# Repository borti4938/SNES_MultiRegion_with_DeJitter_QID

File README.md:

## Multi-Region Mod for any SNES

**Free your SNES**

(picture shows last prototype PCB installed on a SNS-CPU-RGB-01)

### Acknowledgement and Licensing

This PCB, its idea and design, is a confluence of multiple projects. All credits and rights are going to their respective creators:

- **SuperCIC-lock** by Ikari_01
  Copyright (c) 2010 by Maximilian Rehkopf under GNU GPLv2
  Source: [sd2snes homepage](https://sd2snes.de/blog/cool-stuff/supercic)
- **uIGR** by Ikari_01 and borti4938
  Copyright (c) 2010 by Maximilian Rehkopf under GNU GPLv2,
  and modifications copyright (c) 2015 by Peter Bartmann under GNU GPLv2
  Source: [sd2snes homepage](https://sd2snes.de/blog/cool-stuff/in-game-reset), [this repository](./fw/uIGR)
- **Region Patch** built in SNES by Ikari_01 (initial idea and detection using SuperCIC-lock) and borti4938 (schematic refinement and CPLD implementation)
  Initial idea (c) 2012 ikari_01, CPLD implementation as used here covered in DeJitter license
  Source: [sd2snes homepage](https://sd2snes.de/files/supercic-213f.pdf)
- **DeJitter** by marqs85
  Copyright (c) 2017-2018 Markus Hiienkari under MIT
  and modifications and additions copyright (c) 2019 Peter Bartmann under MIT
  Source: [Original GitHub Repository](https://github.com/marqs85/snes_dejitter), [this repository](./fw/Logic)
- **DFO** by micro
  Copyright / created 2015 by Jakob Schäfer without licensing (but given to retro community)
  Source: mirror in [this repository](./fw/dfo), with minor adaptations and with several original sources noted [in the Source.md file](./fw/dfo/SOURCE.md)
- **PCB design** by borti4938
  Copyright (c) 2019 by Peter Bartmann under GNU GPLv3

### Features and Functions

##### In short

- **SuperCIC:** lockout chip replacement 50Hz/60Hz switch cabability
- **uIGR:** controller input sniffing to perform certain actions like reset or 60Hz and 50Hz switch up on certain combinations
- **Region Patch:** overrides region protection based on picture processing status reads
- **DeJitter:** removes jitter on sync for NTSC mode
- **DFO:** dual frequency oscillator, here used to switch between base clocks for 50Hz, 60Hz video-modes

##### SuperCIC

Hold down the reset button in order to swipe through 50Hz (green LED), 60Hz (red LED) or Auto-Region (yellow LED).

With the sd2snes you are able to pair the SuperCIC with the flash card. Then you'll be able to switch between 60Hz and 50Hz mode. However, you need to have the uIGR, which is master for the region setting, in SuperCIC pass through mode. Some more information is given [below](https://github.com/borti4938/SNES_MultiRegion_with_DeJitter_QID#using-a-modded-snes-with-flashcards).

##### uIGR

The uIGR sniffs the controller inputs directly at the controller port. Therefor it is able to detect certain button combinations. All button combinations are collected in an overview PDF, which is available in [German](https://github.com/borti4938/SNES_MultiRegion_with_DeJitter_QID/blob/master/fw/uIGR/Manuals/uIGR_Anleitung.pdf) and [English](https://github.com/borti4938/SNES_MultiRegion_with_DeJitter_QID/blob/master/fw/uIGR/Manuals/uIGR_Manual.pdf). Here are the most important ones:

- Region forcing:
  - 60Hz: L + R + Select + A
  - 50Hz: L + R + Select + Y
  - Auto: L + R + Select + B
  - S-CIC pass through: L + R + Select + D-pad left OR L + R + Select + D-pad right
- Reset:
  - simple reset: L + R + Select + Start
  - double reset (back to main menu of sd2snes): L + R + Select + X

##### Region Patch

Overwrites region if game request register $213F, where bit 4 represents the region. Region patching can be disabled (see [uIGR PDFs](https://github.com/borti4938/SNES_MultiRegion_with_DeJitter_QID/tree/master/fw/uIGR/Manuals)). You also have to consider switching off the region patch if using non-original cartridges or [flash cards](https://github.com/borti4938/SNES_MultiRegion_with_DeJitter_QID#using-a-modded-snes-with-flashcards) (sd2snes with Pairmode with SuperCIC is not a problem).

##### DeJitter

In NTSC mode the SNES outputs a shorter scanline in non-visible area. This might be an issue for certain TVs if you use pure analog to digital conversion without frame buffer like the OSSC does. DeJitter 'removes' this shorter line by pausing the clock for a few cycles.

As drawback this mechanic varies output timing a bit, however the inaccuracy is neglectable when comparing it to clock variations throughout different consoles.

At the moment, DeJitter is enabled by default and can only be disabled by setting jumper _SJ31_.

##### DFO

Short for dual frequency oscillator. Actually in combination with the CPLD this allows to switch between three output clocks plus two color carrier clocks. If modding board is correctly installed, there is nothing special to consider here.

### PCB Description

#### Solder Pads

These are just general descriptions of the in- and outputs. Please refer to the installation instructions for each [specific mainboard version](./installation/) (if exists) for suitable connections.

- **/Rst.o:** (output (2x))
  Low-active reset output. This has to be connected with CIC-lock pad 10 / S-APU pin 100. Connect either pad.
- **Rst.i:** (input)
  High-active reset input. This pad has to be connected with the CIC-lock pad 8 (reset button).
- **LED.Re:** (output)
  LED driver for replacement LED; usually red. Output is active on 60Hz and auto video mode and off on 50Hz (or vice versa if SJ21 is set (common anode LED))
- **LED.Gr:** (output)
  LED driver for replacement LED; usually green. Output is active on 50Hz and auto video mode and off on 60Hz (or vice versa if SJ21 is set (common anode LED))
- **Ctrl.port.10:** (input)
  Input for controller 1 sniffing (data latch signal). _Port_ refers to flat cable connector of the whole controller panel, i.e. pin is equivalent for controller connector pin 3.
- **Ctrl.port.8:** (input)
  Input for controller 1 sniffing (data clock signal). _Port_ refers to flat cable connector of the whole controller panel, i.e. pin is equivalent for controller connector pin 2.
- **Ctrl.port.6:** (input)
  Input for controller 1 sniffing (serial data signal). _Port_ refers to flat cable connector of the whole controller panel, i.e. pin is equivalent for controller connector pin 4.
- **Vmode:** (output)
  Output sets the PPU video mode at S-PPU1 pin 24 and S-PPU2 pin 30 or at the S-CPUN pin 111. Output is active on 50Hz mode and inactive on 60Hz mode.
- **/Vmode:** (output (2x))
  Output sets the video encoding at the video encoder, which is pin 19 of the S-ENC and pin 9 of the S-RGB. Connect just on of the pads!
- **Clk.CIC:** (input)
  Input for the SuperCIC-lock clock, which comes from CIC pad 7.
- **MClk.o:** (output)
  Output for the (de-jittered) master clock of the SNES. This is approx. 21.477MHz in NTSC mode and appr. 17.734MHz (1Chip-SNES, SJ32 not set) or appr. 21.281MHz (non-1Chip, SJ32 set) in PAL mode. Please refer to the general installation note to see whether and how to connect this pad properly.
- **CClk.o:** (output)
  Output of the color carrier, which is appr. 3.380MHz in NTSC mode and appr. 4.433MHz in PAL mode. Please refer to the general installation note to see whether and how to connect this pad properly.
- **/CS.i:** (input (2x since SMR20190813)
  Input of the 'original' (non-de-jittered) composite sync. This comes from pin 100 S-PPU2 or pin 151 S-CPUN.
- **/CS.o buf:** (output)
  Buffered (de-jittered) composite sync output. This is meant to be connected directly to the multiout pin 3. Note: The PAL SNES has 12V connected to this pin, which has to be removed.
- **/CS.o raw:** (output (2x))
  Raw output of the CPLD, which has 3.3V high and 0V low level. Connect it to the video encode, which is pin 8 of the S-ENC or pin 7 of the S-RGB (both chips allows 2.0V for input high, so 3.3V high is sufficient.)

#### Jumper

- **SJ11:** alternative clock for the SuperCIC; close this jumper if you don't connect the _Clk.CIC_ pad in order to use the clock meant for the CIC-key
- **SJ21:** close this jumper if you use a LED with a common anode. Otherwise leave this jumper untouched
- **SJ31:** closing this jumper permanently disables the de-jitter function. This solder jumper is a bit larger to give the installer the option to connect a slide switch here (_speed-runner discussions_).  
   - There is also an issue opened in [marqs85 DeJitter repository](https://github.com/marqs85/snes_dejitter/issues/9) reported by [BambooShadow](https://github.com/BambooShadow), which states that composite video and s-video becomes flickery. This is probably related to the S-RGB encoder chip on SNS-CPU-RGB-01 and later models (PAL: SNSP-CPU-1CHIP-01 and later). In any case, you can disable DeJitter if this is also an issue for you.  
   - I personally recommend to turn DeJitter off. Turn DeJitter only on if you use simple line doublers like the OSSC and if you have any issue on getting a proper picture.
- **SJ32:** short this jumper if the board is installed in a non-1Chip-SNES (SNES Jr. / SNES2 are also 1Chip-SNES)
- **SJ61:** distributes clock output to cartridge slot pin 1. This jumper **must not** be closed in 1Chip-SNES. Side note: if SJ32 is open, SJ61 has to open, too.
- **SJ63:** (since SMR20200323) decides which color carrier is forwarded to output. This jumper has two option; you must not close both jumpers!
  - SJ63.1: (marked with a dot) outputs color carrier derived from non-dejittered clock.  
    Use this if you have a problem with discoloring on composite video or S-Video ([issue thread at shmups](https://shmups.system11.org/viewtopic.php?p=1389666#p1389666))  
    Btw: this is default for all earlier version of the modding board flashed with the current firmware. If you need the other color carrier, just go back to a previous version.
  - SJ63.2: outputs color carrier derived from dejittered clock.  
    (I personally need to use this clock as my TV does not like the color carrier from non-dejittered clock)
  - Again: **You must not close both jumpers!**
- **SJ93**: (since SMR20200323) controls sync level of buffered csync output. Sync level:
  - opened: appr. 1.87V @ 75ohm termination i.e. needs a resistor inside the sync wire further attanuating the signal. Designed to work for cables with 470 ohm resistor inside resulting in appr. 450mV @ 75ohm termination
  - closed: appr. 300mV @ 75ohm termination suitable for pass through wired cables at sync, works with standard TV / scaler setup

#### Firmware

U1, U2, U3 and U5 need a firmware flashed to the chip. U1 and U2 have to be programmed prior to assembly whereas the PCB provides ICSP headers for the other ones.

- **U1:** PIC 16F630 microcontroller with - [SuperCIC-lock firmware](http://sd2snes.de/files/supercic.zip)
- **U2:** PIC 16F684 microcontroller with [uIGR firmware](https://raw.githubusercontent.com/borti4938/SNES_MultiRegion_with_DeJitter_QID/master/fw/uIGR/snes_uigr_684_with_lock.hex)

Use a PICKit, TL866CS or similar programmer.

- **U3:** _ATMEL_ CPLDs: ATF1502ASV or ATF1504ASV(L) CPLD with clock switch, region patch and de-jitter firmware. Pre-build firmware only supports SMR20190813 (and later) modding boards.

  - [ATF1502ASV](https://github.com/borti4938/SNES_MultiRegion_with_DeJitter_QID/raw/master/fw/Logic/output_files/multi_func_atmel/multi_function.svf)
  - [ATF1504ASV(L)](https://github.com/borti4938/SNES_MultiRegion_with_DeJitter_QID/raw/master/fw/Logic/output_files/multi_func_atmel/multi_function_64.svf)
  
Use an OpenOCD compatible JTAG programmer. I tested the workflow with an [Adafruit FT232H Breakout Board](https://www.adafruit.com/product/2264), yet you can use any other JTAG programmer that supports 3.3V IO signal levels.

1. Create an openocd.conf that matches your JTAG programmer. A configuration files for FT2232-based and FT2232H programmers are found in the [firmware folder](./fw/Logic/output_files/multi_func_atmel/). They use following standard pinout for data signals:  
  - ADBUS0 -> TCK
  - ADBUS1 -> TDI
  - ADBUS2 -> TDO
  - ADBUS3 -> TMS
2. Connect the JTAG programmer the modding board, except for Vref! Power the board via 5V during programming.  This can be done by using the DFO programmer connected with V_target set to 5V (or 3.3V) if the modding board is not installed yet (other power solutions are possible, but please use the 5V power supply rail to not harm the DC converters. Or you can simply switch on the SNES for programming. Of course, the CPLD can be also flashed prior to assembly if you have a proper adapter at hand.
3. Initialize the JTAG connection:  
~~~~
openocd -f openocd-ft2232h.conf
~~~~  
OpenOCD should detect the JTAG chain without any errors. If you have any, just double-check if everything is well connected and the CPLD is powered.

4. When successful, open another terminal to interact with openocd and program the chip:  
~~~~
telnet localhost 4444
> svf <full_path_to_svf_file>
~~~~  
Wait for the program to be finished.

- **U3:** _obsolete Altera / intelFPGA CPLDs_: EPM7032 or EPM7064 CPLD with clock switch, region patch and de-jitter firmware. You have to choose the right one depending on your modding board version.

  - [Version SMR20190813 (and later), EPM7032](https://github.com/borti4938/SNES_MultiRegion_with_DeJitter_QID/raw/master/fw/Logic/output_files/multi_func/multi_function.pof)
  - [Version SMR20190813 (and later), EPM7032](https://github.com/borti4938/SNES_MultiRegion_with_DeJitter_QID/raw/master/fw/Logic/output_files/multi_func/multi_function_64.pof)
  - [Version SMR20190603 and earlier](https://github.com/borti4938/SNES_MultiRegion_with_DeJitter_QID/raw/master/fw/Logic/output_files/multi_func_legacy/multi_func_legacy.pof)

Use an Altera USB Blaster (or clone) for flashing the firmware.

After assembly, the modding board has to be powered for flashing the firmware. This can be done by using the DFO programmer connected with V_target set to 5V (or 3.3V) if the modding board is not installed yet (other power solutions are possible, but please use the 5V power supply rail to not harm the DC converters. Or you can simply switch on the SNES for programming. Of course, the CPLD can be also flashed prior to assembly if you have a proper adapter at hand.

- **U5:** CDCE913 with [appropriate configuration](https://raw.githubusercontent.com/borti4938/SNES_MultiRegion_with_DeJitter_QID/master/fw/dfo/clockpro/snes_multi_region.hex)

Use the DFO programmer to flash the PLL. The [DFO readme](./fw/dfo/SOURCE.md) describes how to properly perform the flashing.
I alternatively wrote a [program for Arduino boards](./fw/dfo/arduino/) to flash the CDCE913 with the I2C interface of the Arduino.
I tested the code with an Arduino Nano and Arduino Nano Every.

### Installation Notes

#### Manufacturing the PCB

You can choose any manufacturer which you prefer. All files for manufacturing including the design files are provided in subfolder [pcb/gerber/pcb/](./pcb/gerber/pcb/). As the PCB is designed in EAGLE (current version 7.4.2), gerbers are exported in the actual format. However, some services have problem while automatically analyze those like OSHPark or JCLPCB. Please try the older format in [pcb/gerber/pcb.eagle_legacy_export/](./pcb/gerber/pcb.eagle_legacy_export/).

**IMPORTANT**
Please use a substrate thickness of 0.8mm in order to make installation easier.

#### Assembly

##### Sourcing the Parts

For sourcing the parts, please be referred to the [Bill Of Materials](https://github.com/borti4938/SNES_MultiRegion_with_DeJitter_QID/blob/master/pcb/BOM.xlsx?raw=true)

##### Soldering

The PCB is designed with having hand soldering in mind. Most complicated footprints are probably the 44TQFP package of the CPLD or the 14TSSOP of the CDCE913.

However, if you plan to use a stencil, you can use the [stencil gerber file](./pcb/gerber/stencil/SNES_MR_DeJitter_QID.GTP). All SMDs are placed in top layer.

**IMPORTANT**
SuperCIC (PIC16F630-I/SL) and uIGR (PIC16F684-I/SL) need firmware flashed prior to soldering as mentioned later in this document.

#### Installation

This is not a complete installation manual. It's moreover a general overview on _'HowTo'_. Installation manuals are provided in the [subfolder installation](./installation/) once ready. I cannot test every single mainboard revision (there are too many out there), so the installation folder will grow from time to time once I see a proper report of an installation or I did an installation on a specific mainboard version on my own.

##### Preparation of SNES

###### General Steps

- remove original CIC-lock (or at least lift pins 1, 2, 10 and 11)
- remove LED from front panel (large SNES only)

###### Specific Steps for 1Chip-SNES

- lift pin 111 from S-CPUN
- remove X1
- lift pin 9 from S-RGB (or cut encoding mode jumper at bottom side of SNES mainboard (NTSC board revisions))

###### Specific Steps for Non-1Chip-SNES

- lift pin 24 of S-PPU1 and pin 30 of S-PPU2
- disconnect Master-Clock
  - SNSP-CPU-01/02: lift pin 4 of the S-CLK or remove R73 (0ohm jumper)
  - different methods for NTSC mainboards
- lift CSYNC input pin of the video encoder
  - pin 8 of S-ENC
  - pin 7 of S-RGB
- if you want to switch color carrier:
  - PAL: lift pin 5 of the S-CLK
  - NTSC: lift pin 3 of the S-PPU2
  - SNES with S-ENC: lift pin 19 (or cut encoding mode jumper at bottom side of SNES mainboard (NTSC board revisions))
  - SNES with S-RGB: lift pin 9 (or cut encoding mode jumper at bottom side of SNES mainboard (NTSC board revisions)) 

##### Installation of PCB

###### General Steps

- Solder PCB in place under the cartridge slot. Be aware of the orientation (pin marking must match)
- put the replacement dual LED where the original was (use a small piece of hot glue if needed)...  
... or in SNES2 / Jr. think of a good place where the replacement LED can be if you want to use it...  
... and connect the common pole to either _Ground_ or _Vcc_ (common cathod or anode, respectively)
- connect pads _Rst.o, Rst.i, LED.Re, LED.Gr, Ctrl.port.10-6, Vmode, /CS.i, /CS.o (raw)_ according to their description
- either connect _Clk.CIC_ pad (preferable) or close jumper _SJ11_
- close jumper _SJ21_ if you use a LED with common anode

###### Specific Step for 1Chip-SNES

- connect _MCLK.o_ to X1 (the side which is connected to S-CPUN pin 9)
- connect _/Vmode_ to S-RGB pin 9
- (color carrier is switched by S-CPUN so there is no need to connect _CClk.o_)

###### Specific Step for Non-1Chip-SNES 

- close _SJ32_ and _SJ61_
- if you plan to switch color carrier:
  - connect _CClk.o_ to either pad 3 of S-PPU2 (NTSC) or to pad 5 of S-CLK (PAL)
  - connect _/Vmode_ to S-ENC pin 19 / S-RGB pin 9 

### Using a Modded SNES with Flashcards

In general, using flashcards like the sd2snes, SuperEverdrive and PowerPak together with the **region patching** activated is not a good idea. I try to explain why!

First of all, one has to understand how a region patch works. In the S-PPU2 register $213F bit 4 shows whether the SNES is running in NTSC-mode or in PAL-mode (set up using S-PPU2 pin 30 or S-CPUN pin 111). Many games are checking this register on start-up (or during the gameplay) and check the value on bit 4. NTSC-games expect a '0' whereas PAL-games a '1'. If the bit does not return the required value, the game ends with _'This gamepak is not designed for your SFC/SNES'_ or similar.
A region patch observes the address bus B and recognizes a request of $213F. Then the patch forces on the data bus bit 4 GND or Vcc by simply 'beating'/'overdriving' the output of the S-PPU2.

An important point is how the region patch 'knows' which value has to be written.
On this modding PCB the SuperCIC-lock outputs the value on pin 3. The bit is determined using the CIC-key found on the cartridge. And this is the point where flash-cards become 'critical' for the region patch. As the SuperCIC-lock only checks the region of the cartridge using the CIC-key, the SuperCIC-lock CANNOT know which region the loaded ROM is. The overwritten value on bit 4 during a $213F request might be incorrect!
As flashcards have there own region patching (at least the sd2snes; I don't own a SuperEverdrive or PowerPak) you can simply switch off the region patch of the modding PCB (using Sel+L+R+Dw; LED-code: red-off-red).

#### A very last remark to the sd2snes:
As the SuperCIC-lock is part of the sd2snes project, there is another solution: the so-called 'Pairmode'.
The pairmode is available with the firmware v0.1.7 preview 4 or later. In the Pairmode the SuperCIC-lock goes into a pairmode-loop with the sd2snes. In this loop, forced region, LED status and the ROM region is constantly updated.

To change the forced region (and thus the LED-state) using the sd2snes (via the config.yml or the option GUI -> SuperCIC Settings), the uIGR has to be in the SuperCIC-mode (using Sel+L+R+Le / Sel+L+R+Ri) as the uIGR is master and the SuperCIC-lock slave regarding the region set to the SNES.
As the ROM region is updated constantly, the region patch on the modding PCB can be left on. I recommend to switch the sd2snes-own region patch off in this case (via the config.yml or the option GUI -> In-game Settings).

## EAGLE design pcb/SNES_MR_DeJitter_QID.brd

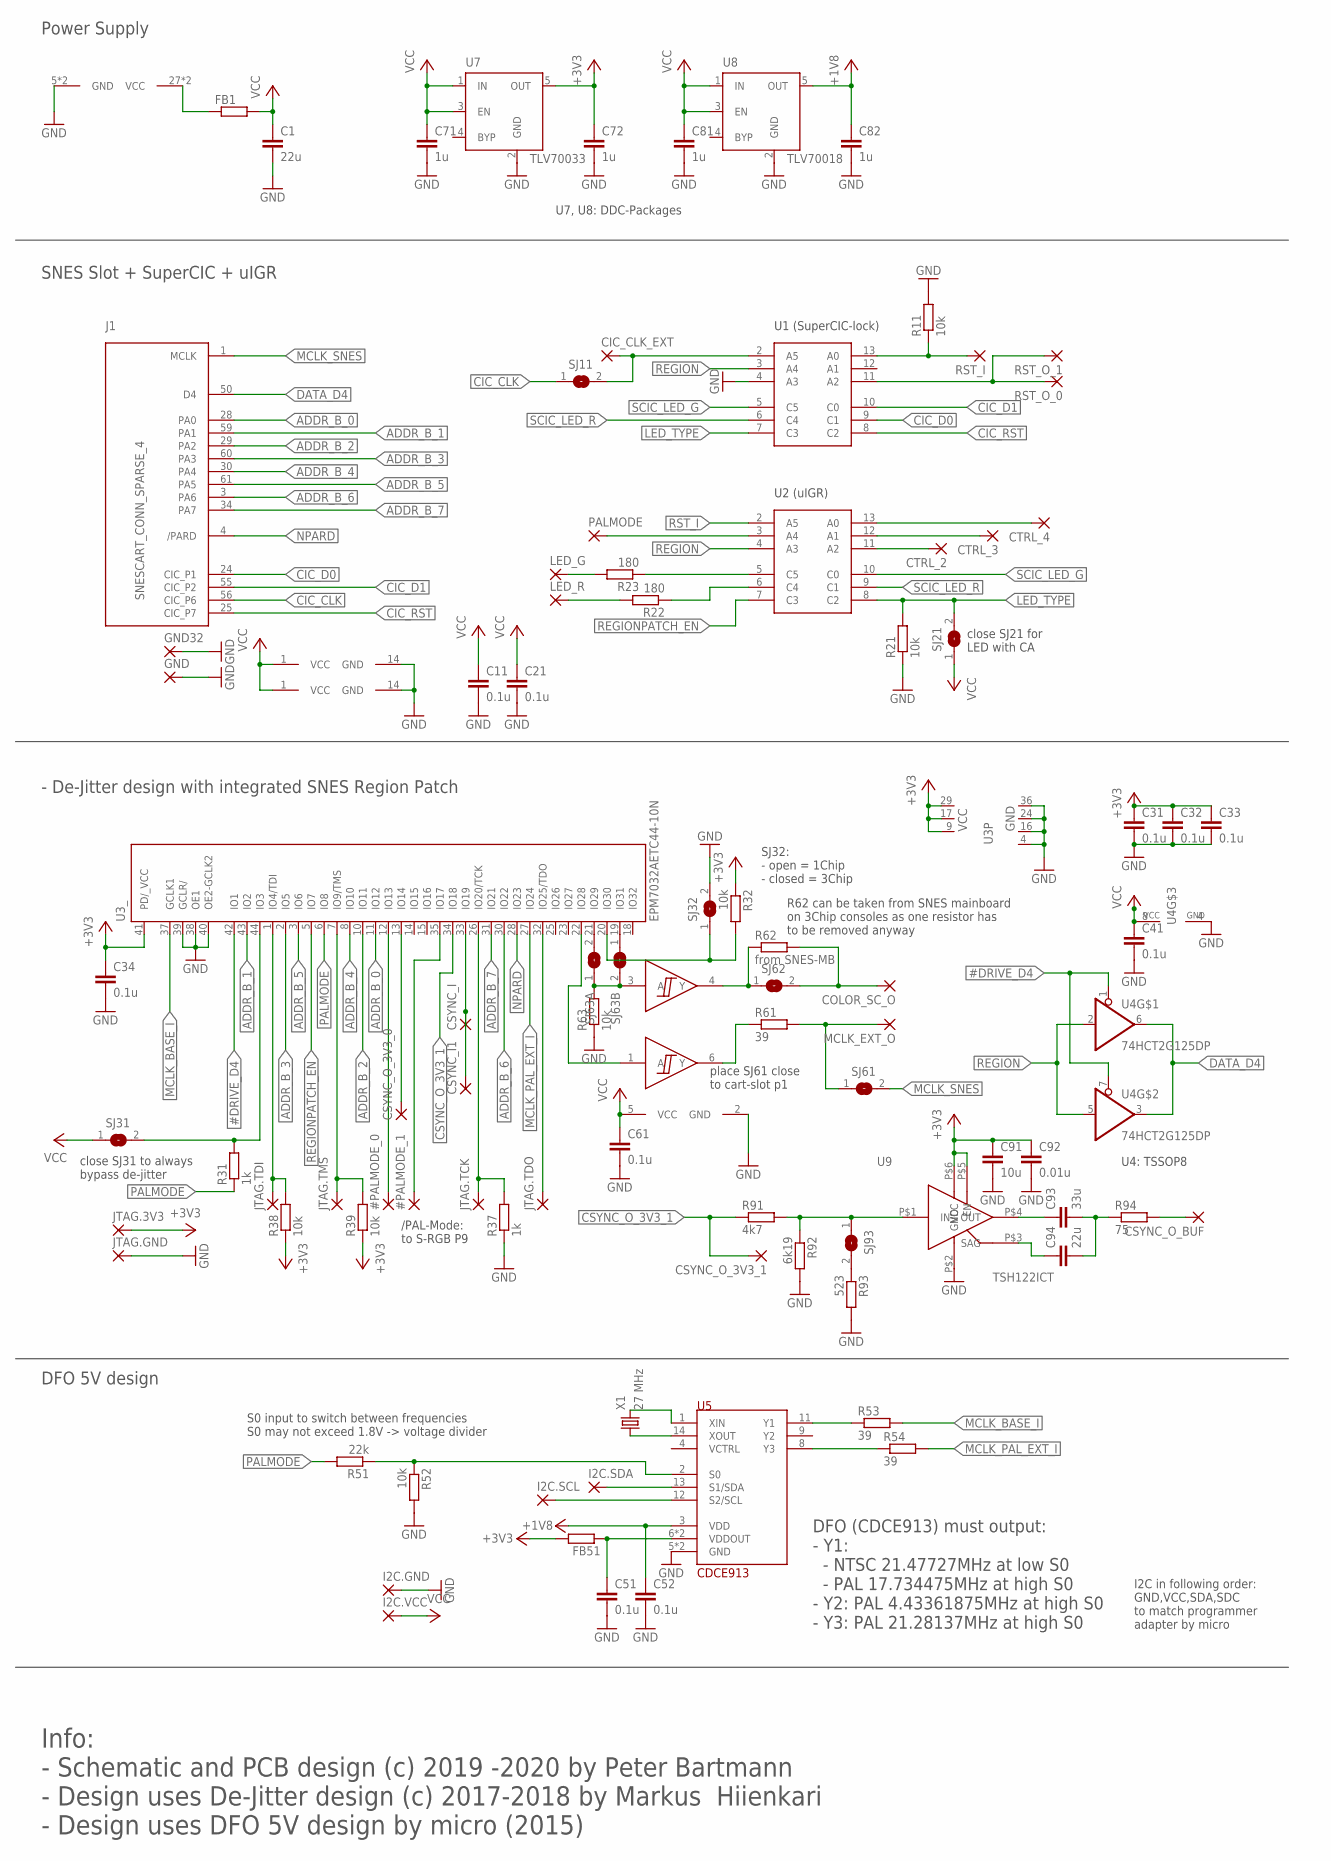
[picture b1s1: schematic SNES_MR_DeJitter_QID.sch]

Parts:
#PALMODE_0, #PALMODE_1: SMD2; SMD1,27-2,54
C1, C94: 22u; C0603
C11, C21, C31, C32, C33, C34, C41, C51, C52, C61: 0.1u; C0603
C71, C72, C81, C82: 1u; C0603
C91: 10u; C0603
C92: 0.01u; C0603
C93: 33u; C0805
CIC_CLK_EXT: SMD2; SMD1,27-2,54
COLOR_SC_O: SMD2; SMD1,27-2,54
CSYNC_I, CSYNC_I1: SMD2; SMD1,27-2,54
CSYNC_O_3V3_0, CSYNC_O_3V3_1: SMD2; SMD1,27-2,54
CSYNC_O_BUF: SMD2; SMD1,27-2,54
CTRL_2, CTRL_3, CTRL_4: SMD2; SMD1,27-2,54
FB1, FB51: R-EU_R0603; R0603
GND, GND32: SMD2; SMD1,27-2,54
I2C.GND, I2C.SCL, I2C.SDA, I2C.VCC: 1,6/0,8
J1: SNESCART_CONN_SPARSE_4
JTAG.3V3, JTAG.GND, JTAG.TCK, JTAG.TDI, JTAG.TDO, JTAG.TMS: 1,6/0,8
LED_G: SMD2; SMD1,27-2,54
LED_R: SMD2; SMD1,27-2,54
MCLK_EXT_O: SMD2; SMD1,27-2,54
PALMODE: SMD2; SMD1,27-2,54
R11, R21, R32, R38, R39, R52: 10k; R0603
R22, R23: 180; R0603
R31, R37: 1k; R0603
R51: 22k; R0603
R53, R54, R61: 39; R0603
R62: from SNES-MB; R0805
R63: 10k; R0805
R91: 4k7; R0603
R92: 6k19; R0603
R93: 523; R0603
R94: 75; R0603
RST_I: SMD2; SMD1,27-2,54
RST_O_0, RST_O_1: SMD2; SMD1,27-2,54
SJ11, SJ21, SJ32, SJ61, SJ62, SJ63A, SJ63B, SJ93: SJSMALL; SJ_SMALL
SJ31: SJ
U1: SuperCIC_lock; PIC16F630
U2: uIGR; PIC16F630
U3: EPM7032AETC44-10N; TQFP44
U4: 74HCT2G125DP; SSOP08
U5: CDCE913; TSSOP14
U6: 2G17TI_DBV; SOT-23-6
U7: TLV70033; SOT23-5
U8: TLV70018; SOT23-5
U9: TSH122ICT; SC70
X1: 27 MHz; HC49UP

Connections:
#DRIVE_D4: U3.42 (IO1), U4.1 (OE), U4.7 (OE)
+1V8: C52.1, C82.1, U5.3 (VDD), U8.5 (OUT)
+3V3: C31.1, C32.1, C33.1, C34.1, C72.1, C91.1, C92.1, FB51.2, JTAG.3V3.1, R32.1, R38.1, R39.1, U3.9 (VCC), U3.17 (VCC), U3.29 (VCC), U3.41 (PD/_VCC), U7.5 (OUT), U9.P$5 (EN), U9.P$6 (VCC)
+5V: C1.1, C11.1, C21.1, C41.1, C61.1, C71.1, C81.1, FB1.2, I2C.VCC.1, SJ21.1, SJ31.1, U1.1 (VCC), U2.1 (VCC), U4.8 (VCC), U6.5 (VCC), U7.1 (IN), U7.3 (EN), U8.1 (IN), U8.3 (EN)
+5V_SNES: FB1.1, J1.27 (VCC), J1.58 (VCC)
ADDR_B_0: J1.28 (PA0), U3.11 (IO12)
ADDR_B_1: J1.59 (PA1), U3.43 (IO2)
ADDR_B_2: J1.29 (PA2), U3.10 (IO11)
ADDR_B_3: J1.60 (PA3), U3.2 (IO5)
ADDR_B_4: J1.30 (PA4), U3.8 (IO10)
ADDR_B_5: J1.61 (PA5), U3.3 (IO6)
ADDR_B_6: J1.3 (PA6), U3.30 (IO22)
ADDR_B_7: J1.34 (PA7), U3.31 (IO21)
CIC_CLK: J1.56 (CIC_P6), SJ11.1
CIC_CLK_EXT: CIC_CLK_EXT.1, SJ11.2, U1.2 (A5)
CIC_D0: J1.24 (CIC_P1), U1.9 (C1)
CIC_D1: J1.55 (CIC_P2), U1.10 (C0)
CIC_RST: J1.25 (CIC_P7), U1.8 (C2)
COLOR_SC_OPT_O_PRE: SJ63B.1, U3.19 (IO31)
COLOR_SC_O_PRE: SJ63A.2, U3.21 (IO29)
COLOR_SC_PCB_O: COLOR_SC_O.1, R62.2, SJ62.2
COLOR_SC_PCB_O_PRE: R62.1, SJ62.1, U6.4 (Y)
COLOR_SC_PRE: R63.2, SJ63A.1, SJ63B.2, U6.3 (A)
CSYNC_I: CSYNC_I.1, CSYNC_I1.1, U3.33 (IO19)
CSYNC_O: CSYNC_O_BUF.1, R94.2
CSYNC_O_3V3_0: CSYNC_O_3V3_0.1, U3.13 (IO14)
CSYNC_O_3V3_1: CSYNC_O_3V3_1.1, R91.1, U3.34 (IO18)
CTRL2: CTRL_2.1, U2.11 (A2)
CTRL3: CTRL_3.1, U2.12 (A1)
CTRL4: CTRL_4.1, U2.13 (A0)
DATA_D4: J1.50 (D4), U4.3 (O), U4.6 (O)
DEJITTER_BYPASS: R31.2, SJ31.2, U3.44 (IO3)
GND: C1.2, C11.2, C21.2, C31.2, C32.2, C33.2, C34.2, C41.2, C51.2, C52.2, C61.2, C71.2, C72.2, C81.2, C82.2, C91.2, C92.2, GND.1, GND32.1, I2C.GND.1, J1.5 (GND), J1.36 (GND), JTAG.GND.1, R11.2, R21.1, R37.1, R52.2, R63.1, R92.2, R93.2, SJ32.2, U1.4 (A3), U1.14 (GND), U2.14 (GND), U3.4 (GND), U3.16 (GND), U3.24 (GND), U3.36 (GND), U3.38 (OE1), U3.39 (GCLR/), U3.40 (OE2-GCLK2), U4.4 (GND), U5.5 (GND), U5.10 (GND), U6.2 (GND), U7.2 (GND), U8.2 (GND), U9.P$2 (GND)
LED_G: LED_G.1, R23.2
LED_R: LED_R.1, R22.2
LED_TYPE: R21.2, SJ21.2, U1.7 (C3), U2.8 (C2)
MCLK_BASE_I: R53.2, U3.37 (GCLK1)
MCLK_BASE_I_PRE: R53.1, U5.11 (Y1)
MCLK_EXT_O: MCLK_EXT_O.1, R61.2, SJ61.1
MCLK_EXT_O_PRE: R61.1, U6.6 (Y)
MCLK_EXT_PRE: U3.22 (IO28), U6.1 (A)
MCLK_PAL_EXT_I: R54.2, U3.27 (IO24)
MCLK_PAL_EXT_I_PRE: R54.1, U5.8 (Y3)
MCLK_SNES: J1.1 (MCLK), SJ61.2
unnamed: R91.2, R92.1, SJ93.1, U9.P$1 (IN)
unnamed: U5.1 (XIN), X1.2
unnamed: U5.14 (XOUT), X1.1
unnamed: C94.1, U9.P$3 (SAG)
unnamed: C93.1, U9.P$4 (OUT)
unnamed: C93.2, C94.2, R94.1
unnamed: R93.1, SJ93.2
NPALMODE_0: #PALMODE_0.1, U3.12 (IO13)
NPALMODE_1: #PALMODE_1.1, U3.35 (IO17)
NPARD: J1.4 (/PARD), U3.28 (IO23)
PALMODE: PALMODE.1, R31.1, R51.2, U2.3 (A4), U3.6 (IO8)
PALMODE.1V8: R51.1, R52.1, U5.2 (S0)
REGION: U1.3 (A4), U2.4 (A3), U4.2 (I), U4.5 (I)
REGIONPATCH_EN: U2.7 (C3), U3.5 (IO7)
RST_I: R11.1, RST_I.1, U1.13 (A0), U2.2 (A5)
RST_O: RST_O_0.1, RST_O_1.1, U1.11 (A2)
SCIC_LED_G: U1.5 (C5), U2.10 (C0)
SCIC_LED_R: U1.6 (C4), U2.9 (C1)
SCL: I2C.SCL.1, U5.12 (S2/SCL)
SDA: I2C.SDA.1, U5.13 (S1/SDA)
SEL_SNES_1CHIP: R32.2, SJ32.1, U3.20 (IO30)
TCK: JTAG.TCK.1, R37.2, U3.26 (IO20/TCK)
TDI: JTAG.TDI.1, R38.2, U3.1 (IO4/TDI)
TDO: JTAG.TDO.1, U3.32 (IO25/TDO)
TMS: JTAG.TMS.1, R39.2, U3.7 (IO9/TMS)
UIGR_LED_G: R23.1, U2.5 (C5)
UIGR_LED_R: R22.1, U2.6 (C4)
VDDOUT: C51.1, FB51.1, U5.6 (VDDOUT), U5.7 (VDDOUT)

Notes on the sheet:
/PAL-Mode: to S-RGB P9
DFO (CDCE913) must output: - Y1: - NTSC 21.47727MHz at low S0 - PAL 17.734475MHz at high S0 - Y2: PAL 4.43361875MHz at high S0 - Y3: PAL 21.28137MHz at high S0
place SJ61 close to cart-slot p1
close SJ31 to always bypass de-jitter
close SJ21 for LED with CA
Info: - Schematic and PCB design (c) 2019 -2020 by Peter Bartmann - Design uses De-Jitter design (c) 2017-2018 by Markus Hiienkari - Design uses DFO 5V design by micro (2015)
S0 input to switch between frequencies S0 may not exceed 1.8V -> voltage divider
I2C in following order: GND,VCC,SDA,SDC to match programmer adapter by micro
U1 (SuperCIC-lock)
U2 (uIGR)
DFO 5V design
- De-Jitter design with integrated SNES Region Patch
SNES Slot + SuperCIC + uIGR
Power Supply
U7, U8: DDC-Packages
U4: TSSOP8
SJ32: - open = 1Chip - closed = 3Chip
R62 can be taken from SNES mainboard on 3Chip consoles as one resistor has to be removed anyway

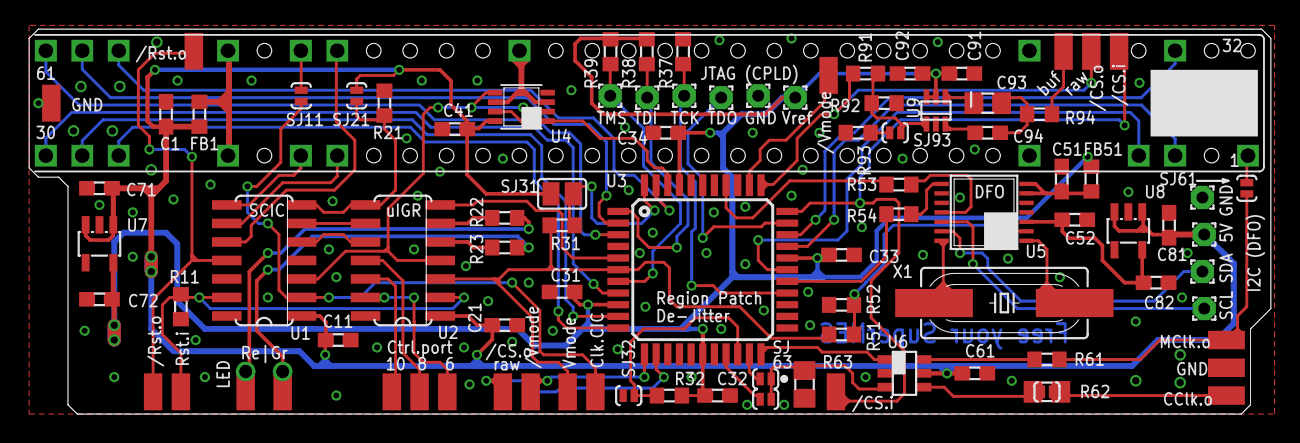
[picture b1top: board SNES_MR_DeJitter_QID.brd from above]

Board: 2 copper layers, 85.2 x 26.4 mm, 92 parts (0 on the bottom side), 72 nets.

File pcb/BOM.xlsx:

Version: | SMR20200325
Number of PCBs: |  |  | 3
Designator | MPN | QTY/PCB | QTY | DESCRIPTION | VALUE | PACKAGE | NOTES | Digikey | Mouser | Firmware
U1 | PIC16F630-I/SL | 1 | 3 | 8bit Microcontroller |  | SOIC-14 | needs SuperCIC-lock firmware preflashed |  |  | http://sd2snes.de/files/supercic.zip
U2 | PIC16F684-I/SL | 1 | 3 | 8bit Microcontroller |  | SOIC-14 | needs uIGR FW preflashed |  |  | https://github.com/borti4938/Switchless-Mods/tree/master/SNE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
U3 | EPM7032AETC44-10N | 1 | 3 | CPLD, 32MCs, 3.3Vcc, 5V tolerant I/Os |  | TQFP44 | fw can be flashed using JTAG header |  |  | https://github.com/borti4938/snes_dejitter/tree/regionpatch%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
U4 | 74HCT2G125DP | 1 | 3 | IC BUFFER NON-INVERT with /OE |  | TSSOP8, SOT505-2
U5 | CDCE913PWR | 1 | 3 | IC PROG PLL VCXO CLK SYN |  | 14TSSOP | I2C accessable over PCB header |  |  | https://github.com/borti4938/SNES-AddOn-PCBs/tree/master/Mul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
U6 | SN74LVC2G17DBVR | 1 | 3 | IC BUFFER NON-INVERT, Schmitt Trigger |  | SOT-23-6
U7 | TLV70033DDCR | 1 | 3 | LDO 3.3V |  | SOT-23-5
U8 | TLV70018DDCR | 1 | 3 | LDO 1.8V |  | SOT-23-5
U9 | TSH122ICT | 1 | 3 | Video Driver, 6dB, 1 Ch. |  | SC-70-6
X1 | 9C-27.000MAAJ-T | 1 | 3 | CRYSTAL 27.0000MHZ 18PF | 27MHz | HC-49/US
C1,C94 | (22uF cap 0603) | 2 | 6 | Ceramic capacitor, X5R | 22uF / 16V | SMD0603
C11,C21,C31,C32,C33,C34,C41,C51,C52,C61 | (100nF cap 0603) | 10 | 30 | Ceramic capacitor, X7R | 0.1uF / 50V | SMD0603
C71,C72,C81,C82 | (1uF cap 0603) | 4 | 12 | Ceramic capacitor, X5R | 1uF / 6.3V | SMD0603
C91 | (10uF cap 0603) | 1 | 3 | Ceramic capacitor, X5R | 10uF / 25V | SMD0603
C92 | (10nF cap 0603) | 1 | 3 | Ceramic capacitor, X7R | 0.01uF / 50V | SMD0603
C93 | (33uF cap 0805) | 1 | 3 | Ceramic capacitor, X5R | 33uF / 5V | SMD0805
FB1,FB51 | MPZ1608S221A | 2 | 6 | Ferrit bead, power line |  | SMD0603
R11,R21,R32,R38,R39,R52,R63 | RC0603FR-0710KL | 7 | 21 | Resistor | 10k | SMD0603
R22,R23 | RC0603FR-07180RL | 2 | 6 | Resistor | 180 | SMD0603
R31,R37 | RC0603FR-071KL | 2 | 6 | Resistor | 1k | SMD0603
R51 | RC0603FR-0722KL | 1 | 3 | Resistor | 22k | SMD0603
R53,R54,R61 | RC0603FR-0739RL | 3 | 9 | Resistor | 39 | SMD0603
R62 |  | 0 | 0 | Resistor / Jumper |  | SMD0805 | resistor taken from SNES mainboard / jumper closed, if CClk.o directly connecte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
R91 | RC0603FR-074K7L | 1 | 3 | Resistor | 4.7k | SMD0603
R92 | RC0603FR-076K19L | 1 | 3 | Resistor | 6.19k | SMD0603
R93 | RC0603FR-07523RL | 1 | 3 | Resistor | 523 | SMD0603
R94 | RC0603FR-0775RL | 1 | 3 | Resistor | 75 | SMD0603
Optional components
(LED) | WP59SURKSGW | 1 | 3 | example replacement LED bi-color with common cathode | red / green
(pin header for LED connection) | 61900211021 | 1 | 3 | pin header for LED connection
 | 61900211621 | 1 | 3 | connector housing 2-pos. Female 2.54mm
 | 61900113722DEC | 2 | 6 | connector socket for 22-28AWG crimp

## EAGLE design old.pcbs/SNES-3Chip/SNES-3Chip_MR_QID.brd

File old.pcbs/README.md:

This is the older version without the CPLD and PLL. No support requests wanted here.

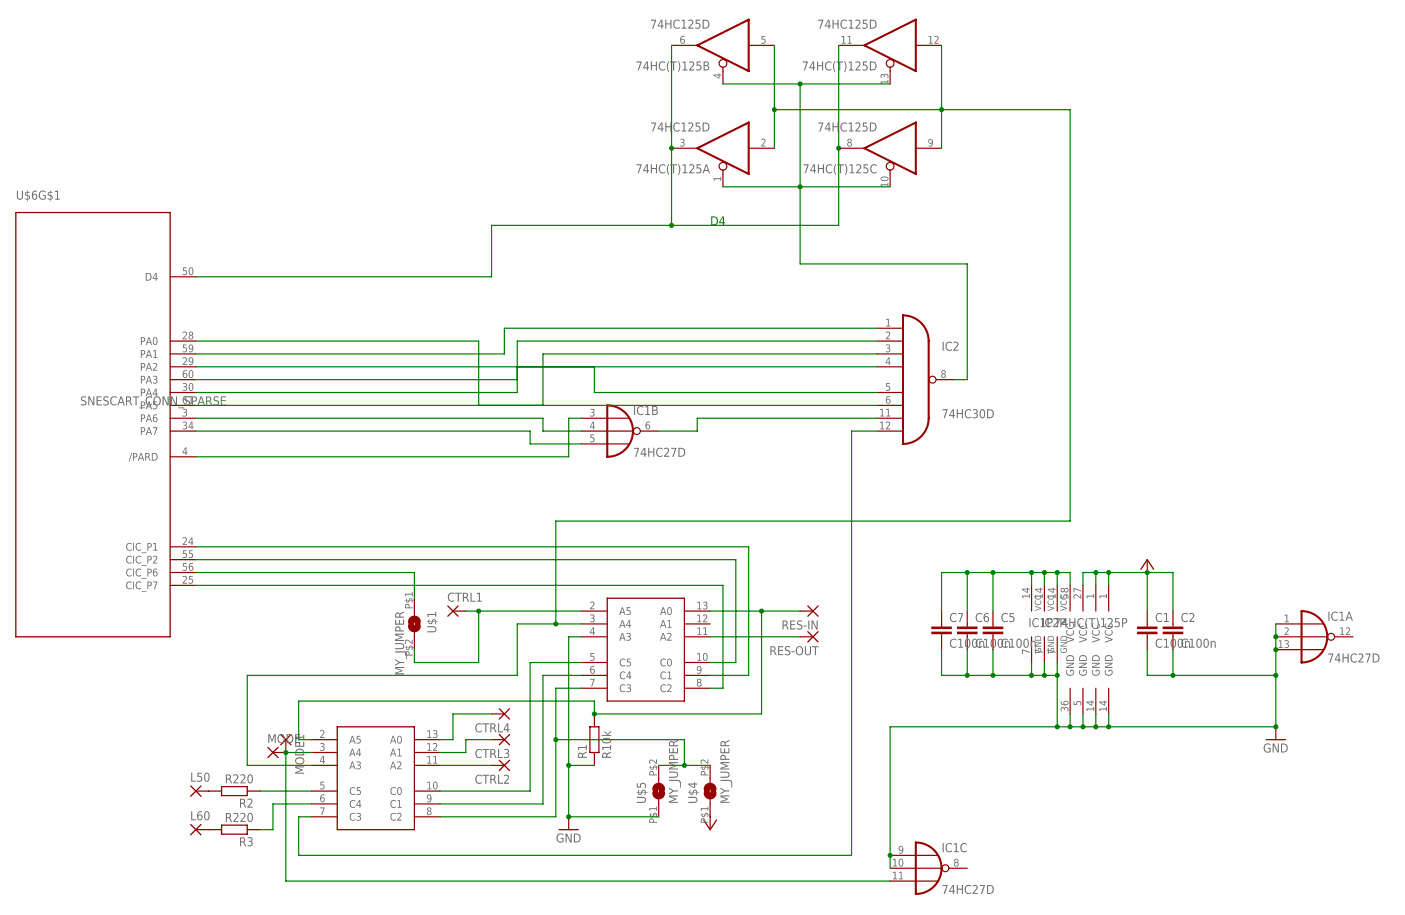
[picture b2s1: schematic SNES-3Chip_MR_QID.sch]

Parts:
74HC(T)125: 74HC125D; SO14
C1, C2, C5, C6, C7: C100n; Z0805
CTRL1, CTRL2, CTRL3, CTRL4: SMD2; SMD1,27-2,54
IC1: 74HC27D; SO14
IC2: 74HC30D; SO14
L50, L60: SMD2; SMD1,27-2,54
MODE, MODE1: SMD2; SMD1,27-2,54
R1: R10k; Z0805
R2, R3: R220; Z0805
RES-IN: SMD2; SMD1,27-2,54
RES-OUT: SMD2; SMD1,27-2,54
U$1, U$4, U$5: MY_JUMPER; MYJUMP
U$2, U$3: PIC16F630_SIMPLE; PIC16F630
U$6: SNESCART_CONN_SPARSE

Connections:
GND: 74HC(T)125.7 (GND), C1.2, C2.2, C5.2, C6.2, C7.2, IC1.1 (I0), IC1.2 (I1), IC1.7 (GND), IC1.9 (I0), IC1.10 (I1), IC1.13 (I2), IC2.7 (GND), R1.1, U$2.4 (A3), U$2.14 (GND), U$3.14 (GND), U$5.P$1 (1), U$6.5 (GND), U$6.36 (GND)
unnamed: 74HC(T)125.1 (OE), 74HC(T)125.4 (OE), 74HC(T)125.10 (OE), 74HC(T)125.13 (OE), IC2.8 (O)
unnamed: RES-OUT.1, U$2.11 (A2)
unnamed: IC2.3 (I2), U$6.61 (PA5)
unnamed: IC2.2 (I1), U$6.60 (PA3)
unnamed: IC1.3 (I0), U$6.4 (/PARD)
unnamed: IC1.4 (I1), U$6.3 (PA6)
unnamed: IC1.6 (O), IC2.11 (I6)
unnamed: IC2.6 (I5), U$6.28 (PA0)
unnamed: R1.2, RES-IN.1, U$2.13 (A0), U$3.2 (A5)
unnamed: L50.1, R2.2
unnamed: R2.1, U$3.5 (C5)
unnamed: R3.1, U$3.6 (C4)
unnamed: IC1.11 (I2), MODE.1, MODE1.1, U$3.3 (A4)
unnamed: L60.1, R3.2
unnamed: IC1.5 (I2), U$6.34 (PA7)
unnamed: IC2.12 (I7), U$3.7 (C3)
unnamed: U$1.P$1 (1), U$6.56 (CIC_P6)
unnamed: U$2.5 (C5), U$3.10 (C0)
unnamed: IC2.1 (I0), U$6.59 (PA1)
unnamed: IC2.5 (I4), U$6.29 (PA2)
unnamed: IC2.4 (I3), U$6.30 (PA4)
unnamed: CTRL2.1, U$3.11 (A2)
unnamed: CTRL3.1, U$3.12 (A1)
unnamed: CTRL1.1, U$1.P$2 (2), U$2.2 (A5)
unnamed: 74HC(T)125.3 (O), 74HC(T)125.6 (O), 74HC(T)125.8 (O), 74HC(T)125.11 (O), U$6.50 (D4)
unnamed: CTRL4.1, U$3.13 (A0)
unnamed: U$2.10 (C0), U$6.55 (CIC_P2)
unnamed: U$2.9 (C1), U$6.24 (CIC_P1)
unnamed: U$2.8 (C2), U$6.25 (CIC_P7)
unnamed: U$2.6 (C4), U$3.9 (C1)
unnamed: U$2.7 (C3), U$3.8 (C2), U$4.P$2 (2), U$5.P$2 (2)
UIGR: 74HC(T)125.2 (I), 74HC(T)125.5 (I), 74HC(T)125.9 (I), 74HC(T)125.12 (I), U$2.3 (A4), U$3.4 (A3)
VCC: C1.1, C2.1, U$2.1 (VCC), U$3.1 (VCC), U$4.P$1 (1), U$6.27 (VCC)
VCC_2: 74HC(T)125.14 (VCC), C5.1, C6.1, C7.1, IC1.14 (VCC), IC2.14 (VCC), U$6.58 (VCC)

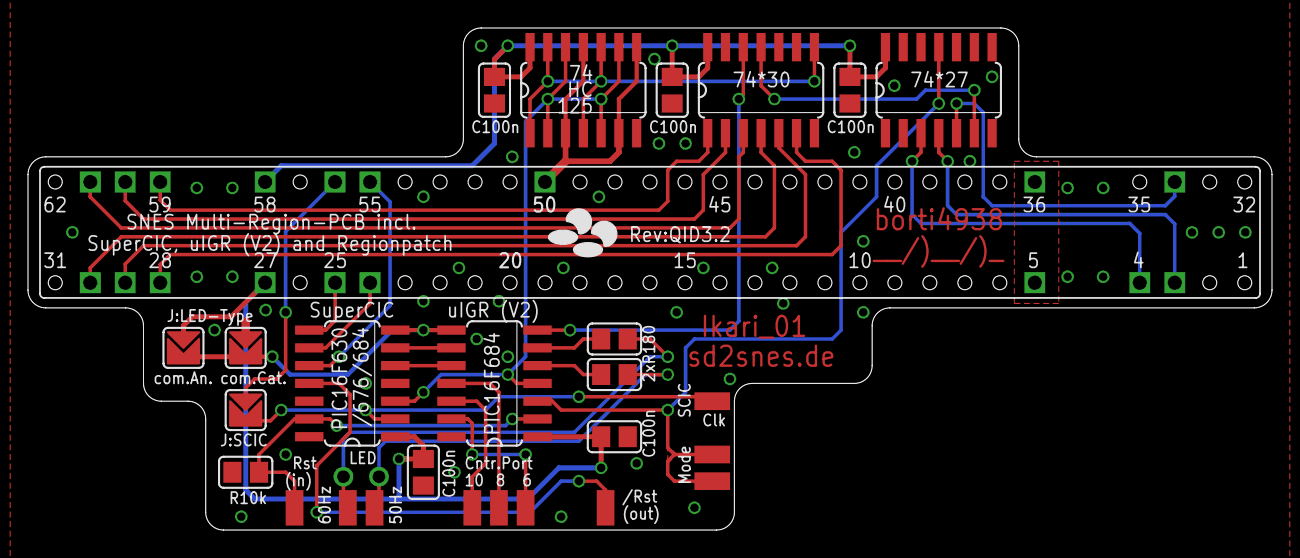
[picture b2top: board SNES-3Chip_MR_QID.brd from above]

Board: 2 copper layers, 88.9 x 35.9 mm, 27 parts (0 on the bottom side), 35 nets.

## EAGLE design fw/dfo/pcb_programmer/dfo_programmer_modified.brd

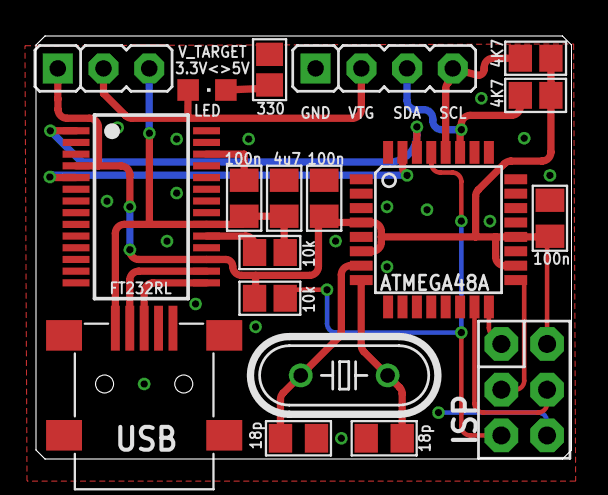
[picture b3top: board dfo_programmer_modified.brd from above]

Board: 2 copper layers, 29.8 x 23.5 mm, 19 parts (0 on the bottom side), 18 nets.

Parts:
C1, C5, C6: 100n; C0805K_B
C2: 4u7; C0805K_B
C3, C4: 18p; C0805K_B
E$1: JP2
IC1: FT232RL; SSOP28
IC2: ATMEGA48A; TQFP32-08
JP1: JP3
LED: CHIPLED_0805
Q1: 10M; HC49/S
R1, R2: 10k; R0805_B
R3, R4: 4K7; R0805_B
R5: 330; R0805_B
U$2: ISPBIG_POGO_PINS; 2X3_ISP_BIGPOGO
USB1: LUMBERG2486_01_MINI_USB_B; LUM2486-01

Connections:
!RESET: IC2.29, R1.2, U$2.RESET
+3V3: C5.2, C6.2, E$1.1, IC1.4, IC1.17, IC2.4, IC2.6, IC2.18, IC2.20, R1.1, R3.2, R4.2, U$2.VCC
FT_RX: IC1.5, IC2.31
FT_TX: IC1.1, IC2.30
GND: C1.1, C2.1, C3.1, C4.1, C5.1, C6.1, IC1.7, IC1.18, IC1.21, IC1.25, IC1.26, IC2.3, IC2.5, IC2.21, JP1.1, R5.2, U$2.GND, USB1.5GND
unnamed: LED.C, R5.1
unnamed: C1.2, C2.2, E$1.3, IC1.20, R2.2, USB1.1VBUS
unnamed: IC1.19, R2.1
unnamed: C3.2, IC2.7, Q1.2
unnamed: C4.2, IC2.8, Q1.1
unnamed: IC2.16, U$2.MISO
unnamed: IC2.17, U$2.SCK
unnamed: IC2.15, U$2.MOSI
S$2: IC2.27, JP1.3, R3.1
SCL: IC2.28, JP1.4, R4.1
USB+: IC1.15, USB1.3D+
USB-: IC1.16, USB1.2D-
V_TARGET: E$1.2, JP1.2, LED.A

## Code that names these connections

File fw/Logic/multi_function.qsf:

# -------------------------------------------------------------------------- #
#
# Copyright (C) 1991-2013 Altera Corporation
# Your use of Altera Corporation's design tools, logic functions
# and other software and tools, and its AMPP partner logic
# functions, and any output files from any of the foregoing
# (including device programming or simulation files), and any
# associated documentation or information are expressly subject
# to the terms and conditions of the Altera Program License
# Subscription Agreement, Altera MegaCore Function License
# Agreement, or other applicable license agreement, including,
# without limitation, that your use is for the sole purpose of
# programming logic devices manufactured by Altera and sold by
# Altera or its authorized distributors.  Please refer to the
# applicable agreement for further details.
#
# -------------------------------------------------------------------------- #
#
# Quartus II 64-Bit
# Version 13.0.1 Build 232 06/12/2013 Service Pack 1 SJ Web Edition
# Date created = 01:40:55  December 16, 2017
#
# -------------------------------------------------------------------------- #
#
# Notes:
#
# 1) The default values for assignments are stored in the file:
#		multi_function_assignment_defaults.qdf
#    If this file doesn't exist, see file:
#		assignment_defaults.qdf
#
# 2) Altera recommends that you do not modify this file. This
#    file is updated automatically by the Quartus II software
#    and any changes you make may be lost or overwritten.
#
# -------------------------------------------------------------------------- #


set_global_assignment -name FAMILY MAX7000AE
set_global_assignment -name DEVICE "EPM7032AETC44-10"
set_global_assignment -name ORIGINAL_QUARTUS_VERSION "13.0 SP1"
set_global_assignment -name PROJECT_CREATION_TIME_DATE "23:07:46  APRIL 07, 2019"
set_global_assignment -name LAST_QUARTUS_VERSION "13.0 SP1.02"
set_global_assignment -name ERROR_CHECK_FREQUENCY_DIVISOR "-1"

set_location_assignment PIN_28 -to NPARD
set_location_assignment PIN_31 -to ADDRESS_BUS_B[7]
set_location_assignment PIN_30 -to ADDRESS_BUS_B[6]
set_location_assignment PIN_3 -to ADDRESS_BUS_B[5]
set_location_assignment PIN_8 -to ADDRESS_BUS_B[4]
set_location_assignment PIN_2 -to ADDRESS_BUS_B[3]
set_location_assignment PIN_10 -to ADDRESS_BUS_B[2]
set_location_assignment PIN_43 -to ADDRESS_BUS_B[1]
set_location_assignment PIN_11 -to ADDRESS_BUS_B[0]
set_location_assignment PIN_42 -to NDRIVE_D4
set_location_assignment PIN_5 -to EN_REGPATCH

set_location_assignment PIN_20 -to SEL_SNES_1CHIP
set_location_assignment PIN_6 -to PALMODE
set_location_assignment PIN_35 -to NPALMODE[1]
set_location_assignment PIN_12 -to NPALMODE[0]

set_location_assignment PIN_37 -to MCLK_base_i
set_location_assignment PIN_27 -to MCLK_PAL_ext_i
set_location_assignment PIN_22 -to MCLK_o
set_location_assignment PIN_19 -to ColorCarrier_opt_o
set_location_assignment PIN_21 -to ColorCarrier_o

set_location_assignment PIN_44 -to DEJITTER_BYPASS
set_location_assignment PIN_33 -to CSYNC_i
set_location_assignment PIN_34 -to CSYNC_o[1]
set_location_assignment PIN_13 -to CSYNC_o[0]


set_global_assignment -name PROJECT_OUTPUT_DIRECTORY output_files/multi_func
set_global_assignment -name TOP_LEVEL_ENTITY snes_mult_func
set_global_assignment -name VERILOG_FILE rtl/snes_mult_func.v
set_global_assignment -name VERILOG_FILE rtl/snes_dejitter_mod.v
set_global_assignment -name SDC_FILE multi_function.sdc

set_global_assignment -name MAX7000_DEVICE_IO_STANDARD "3.3-V LVTTL"
set_global_assignment -name SYNTH_TIMING_DRIVEN_SYNTHESIS OFF
set_global_assignment -name OPTIMIZE_HOLD_TIMING OFF
set_global_assignment -name OPTIMIZE_MULTI_CORNER_TIMING OFF

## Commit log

2020-05-03 initial commit as stand alone project
2020-05-03 minor fixes in redirects
2020-05-03 add older PCB versions
2020-05-04 remove unneccessarily committed files
2020-05-04 color subcarrier fix - initial commit was based on old version here
2020-08-30 resolve inconsistency between schematic and BOM
2020-09-07 DFO programmer to go: - Arduino sketch (e.g. for Arduino Nano Every) - tools (to generate const byte regs[], e.g. for other projects)
2020-09-08 replace some magic numbers
2020-10-22 add short description for features
2020-12-01 write and read registers in bytes (solve issue #2)
2022-03-28 typo fix
2022-04-03 add CPLD with 64MCs
2022-04-03 add firmware build for ATMEL CPLD
2022-04-03 update BOM
2022-04-03 update readme and add openocd config files
2022-04-03 add readme for firmware conversion
2022-04-15 add SHVC-CPU-01 installation instructions
2022-04-18 describe color carrier mod for 1Chip console
2022-04-20 leave here and there remarks on SJ93
2023-08-28 Add instructions and photos for SNS-CPU-GPM-02

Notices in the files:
parts and their libraries:
SparkFun: Licensing: CC v3.0 Share-Alike You are welcome to use this library for commercial purposes.
